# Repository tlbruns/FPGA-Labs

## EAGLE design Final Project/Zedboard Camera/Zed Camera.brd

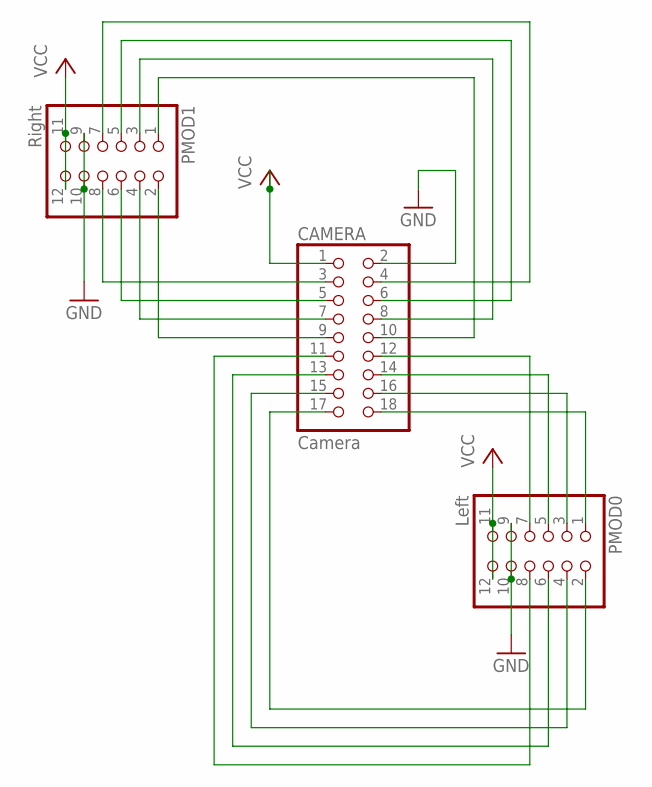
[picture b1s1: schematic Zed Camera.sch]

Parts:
CAMERA: Camera; 2X09
PMOD0: Left; 2X06
PMOD1: Right; 2X06

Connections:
CAMERA: CAMERA.15, PMOD0.4
GND: CAMERA.2, PMOD0.9, PMOD0.10, PMOD1.9, PMOD1.10
unnamed: CAMERA.18, PMOD0.1
unnamed: CAMERA.16, PMOD0.3
unnamed: CAMERA.14, PMOD0.5
unnamed: CAMERA.12, PMOD0.7
unnamed: CAMERA.17, PMOD0.2
unnamed: CAMERA.11, PMOD0.8
unnamed: CAMERA.9, PMOD1.2
unnamed: CAMERA.7, PMOD1.4
unnamed: CAMERA.5, PMOD1.6
unnamed: CAMERA.3, PMOD1.8
unnamed: CAMERA.10, PMOD1.1
unnamed: CAMERA.8, PMOD1.3
unnamed: CAMERA.6, PMOD1.5
unnamed: CAMERA.4, PMOD1.7
unnamed: CAMERA.13, PMOD0.6
VCC: CAMERA.1, PMOD0.11, PMOD0.12, PMOD1.11, PMOD1.12

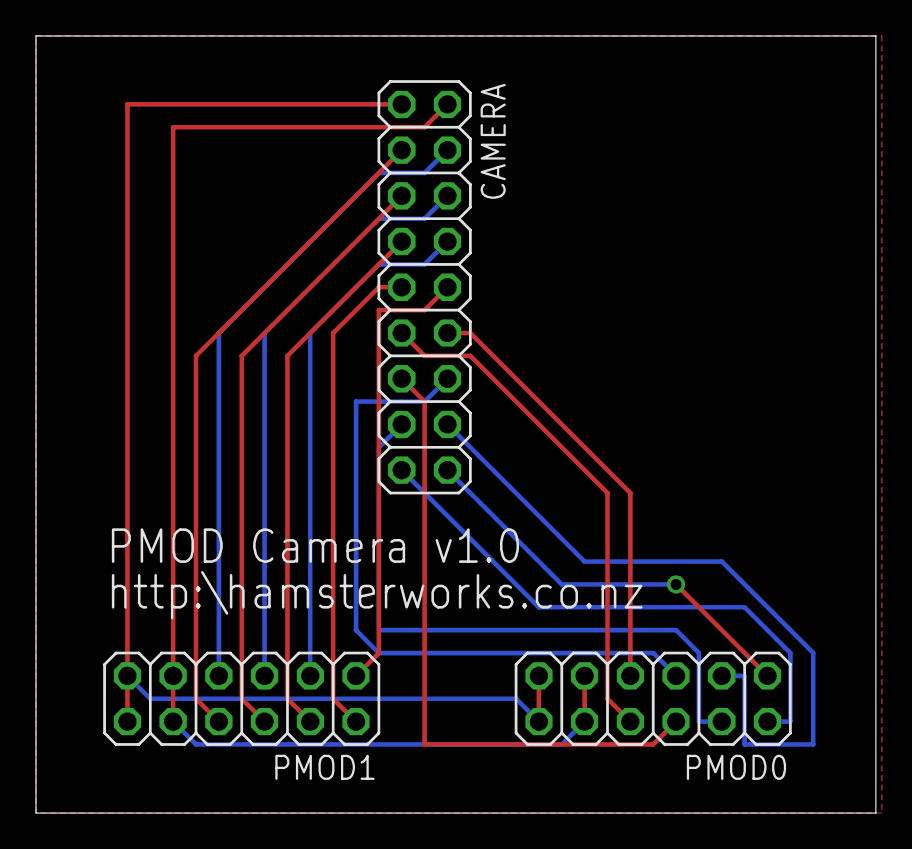
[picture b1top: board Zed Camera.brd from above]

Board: 2 copper layers, 46.7 x 43.2 mm, 3 parts (0 on the bottom side), 18 nets.

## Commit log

2014-10-07 :confetti_ball: Added .gitattributes & .gitignore files
2014-10-07 test bench Q2
2014-10-08 Q1 finished
2014-10-08 Problem 5
    PArt 1
2014-10-08 Q1 and Q2 final
    headers added to all files
2014-10-08 PART3 and the rest
2014-10-08 PART 3 continue
2014-10-08 part3 last
2014-10-09 Part 2 working
2014-10-09 part4
2014-10-09 Part4 almost working
2014-10-09 All but Q5-Part4 finalized
    cleaned up code and added headers
2014-10-10 Finished
2014-10-20 Lab 3 creation
2014-10-20 Q1
    done
2014-10-22 Q5 and Q8
    done
2014-10-24 Q6 Done
2014-10-25 Q7
    ok
2014-10-26 Q7
    not good
2014-10-26 Q7 Def
    Well done
2014-10-26 K
    clean Q7
2014-10-27 Q7 finished
    bug fixed where "i" would print on wrong line due to memory_offset issue
2014-10-27 Revert "Q7 finished"
    This reverts commit 8b8fc3b11895798c907f0cb6e3e9abbd7c3b7adc.
2014-10-27 Revert "Revert "Q7 finished""
    This reverts commit 520ff46e6754b42a8acd60d9d7ec302c7183680b.
2014-10-27 Q4 Ok
2014-10-28 final project V0
2014-10-28 better
2014-10-31 Lab 3- Q1/Q2 finalized
2014-10-31 Lab3- Q5/6/7 finalized
2014-11-01 ok q3
2014-11-01 Ok Q4
2014-11-01 Ok Q6
2014-11-02 Lab 3 Finalized
    SRAM output files tested and placed in separate folder. Entire lab
    zipped for submission
2014-11-04 camera
2014-11-06 some pdf
    s
2014-11-07 LCD
    Works at 25 MHZ , GOOD FOR CAMERA SYNCRONIZATION
2014-11-25 camera_V2
2014-11-25 V2 and LCD
2014-11-25 lcd_Camera working
2014-11-26 ok _camera_lcd
2014-11-26 Datasheets
2014-12-01 Added mouse IP
2014-12-02 Mouse working w/LCD
2014-12-02 Added take_photo icon
2014-12-03 V3_0
2014-12-11 Revert "V3_0"
    This reverts commit a38291ee76baaff429143f895ce6beab6c00293e.
2014-12-11 Revert "Revert "V3_0""
    This reverts commit 855106ac0079df583c630ea7ccecd785af0c9596.
